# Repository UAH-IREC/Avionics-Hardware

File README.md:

# Avionics-Hardware
KiCad projects and libraries for all PCBs flying on the rocket

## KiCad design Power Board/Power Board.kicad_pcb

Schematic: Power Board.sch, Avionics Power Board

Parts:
C1: 470 µF; CP_Radial_Horiz_D8.0mm_L13.00mm_P3.50mm; Digikey Part Number 1189-1733-ND
C2, C3, C4, C5, C6, C7, C20, C21, C22, C23, C29, C30: 0.1 µF; C_0603; Digikey Part Number 1276-6717-6-ND
C8: 0.1 µF; C_0805; Digikey Part Number 478-3351-1-ND
C9, C14: 22 µF; C_0805; Digikey Part Number 1276-6780-1-ND
C10: 47 µF; C_0805; Digikey Part Number 490-13249-1-ND
C11, C12: 22nF; C_0603; Digikey Part Number 399-9044-1-ND
C13: 15 µF; C_0805; Digikey Part Number 445-14373-1-ND
C15: 1 µF; C_0603; Digikey Part Number 1276-6524-1-ND
C16, C17, C25, C26: 4.7 µF; C_0603; Digikey Part Number 1276-1900-1-ND
C18: 270 pF; C_0603; Digikey Part Number 1276-2019-1-ND
C19, C27, C28: 10 µF; C_0603; Digikey Part Number 1276-1038-1-ND
C24: 0.33 µF; C_0603; Digikey Part Number 445-12479-6-ND
D1, D4, D5, D9, D11, D12: 12V TVS; TVS_0603; Digikey Part Number 641-1256-1-ND
D2: SMBJ26A; D_SMB; Digikey Part Number SMBJ26AFSCT-ND
D3, D6, D7, D8: LED_B; LED_0603; Digikey Part Number 160-1647-1-ND
D10, D17, D18: 3.3V TVS; TVS_0402; Digikey Part Number 641-1893-1-ND
D13, D14: LED_R; LED_0603; Digikey Part Number 160-1447-1-ND
D15: D_Schottky; D_SOD-123F; Digikey Part Number CRS08QMCT-ND
D16: LED_G; LED_0603; Digikey Part Number 160-1888-1-ND
H1, H2, H3, H4: M3 Mounting Hole; MountingHole_3.2mm_M3; Digikey Part Number 732-12933-ND
HS1: Heatsink; HS_ATS1099; Digikey Part Number ATS1099-ND
J1: Conn_02x07_Odd_Even; Pin_Header_Straight_2x07_Pitch2.54mm; Digikey Part Number 952-1932-ND
J2: Screw_Terminal_01x06; 3PCV-06; Digikey Part Number 3PCV-06-006-ND
J3: Conn_01x03; JST_XH_S03B-XH-A_03x2.50mm_Angled; Digikey Part Number 455-2250-ND
J4: Conn_01x02; JST_PH_S2B-PH-K_02x2.00mm_Angled; Digikey Part Number 455-1719-ND
J5: Conn_02x03_Odd_Even; Pin_Header_Straight_2x03_Pitch1.27mm_SMD; Digikey Part Number 609-3693-1-ND
L1: 2.2 µH; L_SRP6540; Digikey Part Number SRP6540-2R2MCT-ND
L2: 15 µH; L_Wuerth_7447779115; Digikey Part Number 732-4180-1-ND
L3: 10 µH; L_SLF10165; Digikey Part Number 445-6478-1-ND
L4: 10 µH; L_1008; Digikey Part Number 490-10563-2-ND
L5: 220 Ω @ 100 MHz; L_0603; Digikey Part Number 732-1581-2-ND
Q1, Q2, Q3, Q4, Q5, Q6: SI7157DP; PowerPAK_SO-8; Digikey Part Number SI7157DP-T1-GE3CT-ND
Q7: DMG2305UX; SOT-23; Digikey Part Number DMG2305UX-13DICT-ND
R1, R2, R3, R4, R26: 1 kΩ; R_0603; Digikey Part Number RHM1.0KDCT-ND
R5, R8, R11: 82.5 kΩ; R_0603; Digikey Part Number P82.5KHCT-ND
R6, R9, R12: 5.49 kΩ; R_0603; Digikey Part Number 311-5.49KHRCT-ND
R7, R10, R13: 11 kΩ; R_0603; Digikey Part Number P11.0KHCT-ND
R14, R15, R16, R29, R30, R31: 100 kΩ; R_0603; Digikey Part Number P100KDBCT-ND
R17: 33.2 kΩ; R_0603; Digikey Part Number P33.2KHCT-ND
R18, R34, R35, R36, R38, R39, R43, R44, R45, R49, R50, R51, R53: 10 kΩ; R_0603; Digikey Part Number P10.0KHCT-ND
R19, R28: 100 Ω; R_0603; Digikey Part Number P100HCT-ND
R20: 470 Ω; R_0603; Digikey Part Number P470HCT-ND
R21: 95.3 kΩ; R_0603; Digikey Part Number P95.3KDBCT-ND
R22: 51 kΩ; R_0603; Digikey Part Number P51.0KHCT-ND
R23: 13.3 kΩ; R_0603; Digikey Part Number P13.3KDBCT-ND
R24: 0.124Ω; R_2512; Digikey Part Number A109697CT-ND
R25: 8.25 kΩ; R_0603; Digikey Part Number P8.25KDBCT-ND
R27: 22.1 kΩ; R_0603; Digikey Part Number P22.1KDBCT-ND
R32: 140 kΩ; R_0603; Digikey Part Number P140KDBCT-ND
R33: 10 Ω; R_0603; Digikey Part Number 541-10.0SCT-ND
R37: 2.5 mΩ; R_2512; Digikey Part Number A131768CT-ND
R40, R41, R42, R46, R47, R48, R52: 121 kΩ; R_0603; Digikey Part Number P121KDBCT-ND
R54, R55, R56, R57, R58, R59: 64.9 kΩ; R_0603; Digikey Part Number P64.9KDBCT-ND
SYM1: SYM_Arrow45_XLarge; Logo_v3; Digikey Part Number N/A
TH1, TH2, TH3, TH4, TH5, TH6, TH7: NXFT15XH103FA2B100; Thermistor_Through_Hole_Tiny; Digikey Part Number 490-5630-ND
U1: LTC4417CGN; SSOP-24_3.9x8.7mm_Pitch0.635mm; Digikey Part Number LTC4417CGN#PBF-ND
U2: TPS564208DDCT; SOT-23-6; Digikey Part Number 296-44123-1-ND
U3: LTC3130-1; MSOP-16-1EP_3x4mm_Pitch0.5mm; Digikey Part Number LTC3130IMSE-1#PBF-ND
U4: LMR62014XMF; SOT-23-5; Digikey Part Number LMR62014XMF/NOPBCT-ND
U5: TPS22810; SOT-23-6; Digikey Part Number 296-45304-1-ND
U6: BQ2057WSNTR; SOIC-8_3.9x4.9mm_Pitch1.27mm; Digikey Part Number 296-41202-1-ND
U7: BQ29209DRBT; Texas_S-PVSON-N8; Digikey Part Number 296-49154-1-ND
U8: LT6700CS6-1; TSOT-23-6; Digikey Part Number LT6700CS6-1#TRMPBFCT-ND
U9: STS8C5H30L; SOIC-8_3.9x4.9mm_Pitch1.27mm; Digikey Part Number 497-4398-1-ND
U10: LTC4150; MSOP-10_3x3mm_Pitch0.5mm; Digikey Part Number LTC4150CMS#PBF-ND
U11: ATxmega32E5-AU; TQFP-32_7x7mm_Pitch0.8mm; Digikey Part Number ATXMEGA32E5-AU-ND

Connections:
+3V3: C10.1, D10.1, D13.2 (A), J1.12, J1.14, J5.2, L1.2, L4.1, R14.2, R15.2, R16.2, R17.1, R36.1, R38.1, R39.1, R40.1, R54.1, R55.1, R56.1, R57.1, R58.1, R59.1
+12V: C14.1, D12.1, D14.2 (A), J1.8, R41.1, U3.14 (V_OUT)
/3V3_SENS: R40.2, R43.1, U11.6 (AREF/PA0)
/12V_SENS: R41.2, R44.1, U11.5 (PA1)
/BAL_OUT: U7.8 (OUT), U11.10 (PC6)
/BAT_BAK_VCC: C7.2, D5.1, J2.4, Q5.1 (D), R2.1, R11.2, R47.1, U1.22 (V3)
/BAT_BAK_VCC_SENS: R47.2, R50.1, U11.2 (PA4)
/BAT_CELL_1: J3.2, R31.2, R33.1, R52.1
/BAT_CELL_1_SENS: R52.2, R53.1, U11.30 (PA6)
/BAT_CELL_2: C6.2, C25.2, D4.1, Q3.1 (D), Q7.2, R3.1, R8.2, R28.2, R29.1, R30.2, R32.1, R37.2, R46.1, U1.23 (V2), U6.2 (BAT), U8.5 (Vs), U9.7 (D1), U9.8 (D1), U10.1 (SENSE+), U10.8 (VDD)
/BAT_CELL_2_CONN: J2.1, J3.3, R37.1, U10.2 (SENSE-)
/BAT_CHARGE_EN: R22.2, U4.4 (EN), U5.3, U11.20 (PR0/XTAL2)
/BAT_CHARGE_VCC: C20.1, R24.2, R25.1, U5.6, U6.3 (VCC), U6.8 (COMP)
/BAT_VCC_SENS: R46.2, R49.1, U11.3 (PA3)
/CHARGE_STAT: D16.2 (A), U6.5 (STAT), U11.9 (PC7)
/LVL_POL: R38.2, U10.6 (POL), U11.11 (PC5)
/LVL_~INT~: R36.2, U10.9 (~CLR~), U10.10 (~INT~), U11.12 (PC4)
/LVL_~SHDN~: U10.5 (~SHDN~), U11.13 (PC3)
/MCU_SCL: J1.4, U11.15 (PC1)
/MCU_SDA: J1.2, U11.16 (PC0)
/SEL_~SHDN~: U1.2 (~SHDN), U11.14 (PC2)
/SEL_~VALID1~: R16.1, U1.10 (~VALID1), U11.22 (PD6)
/SEL_~VALID2~: R15.1, U1.11 (~VALID2), U11.21 (PD7)
/SEL_~VALID3~: R14.1, U1.12 (~VALID3), U11.29 (PA7)
/THERM1: R54.2, TH2.2, U11.28 (PD0/AREF)
/THERM2: R56.2, TH4.2, U11.27 (PD1)
/THERM3: R58.2, TH6.2, U11.26 (PD2)
/THERM4: R55.2, TH3.2, U11.25 (PD3)
/THERM5: R57.2, TH5.2, U11.24 (PD4)
/THERM6: R59.2, TH7.2, U11.23 (PD5)
/UMB_VCC: C5.2, C17.1, D1.1, J2.3, L3.1, Q1.1 (D), R4.1, R5.2, R42.1, U1.24 (V1), U4.5 (VIN)
/UMB_VCC_SENS: R42.2, R45.1, U11.4 (PA2)
/VCC_IN: C1.1, C9.1, C13.1, C15.1, D2.1 (K), D9.1, D11.1, J2.6, Q2.1 (D), Q4.1 (D), Q6.1 (D), R1.1, R48.1, U1.15 (VOUT), U2.3 (VIN), U3.4 (PV_IN), U3.5 (V_IN), U3.6 (RUN), U3.8 (MPPC), U3.9 (VS2), U3.10 (VS1), U3.11 (MODE)
/VCC_IN_SENS: R48.2, R51.1, U11.31 (PA5)
GND: C1.2, C2.2, C3.2, C4.2, C5.1, C6.1, C7.1, C9.2, C10.2, C13.2, C14.2, C15.2, C16.2, C17.2, C19.2, C20.2, C22.2, C23.2, C24.2, C25.1, C27.1, C28.2, C29.1, C30.1, D1.2, D2.2 (A), D3.1 (K), D4.2, D5.2, D6.1 (K), D7.1 (K), D8.1 (K), D9.2, D10.2, D11.2, D12.2, D17.1, D18.2, J1.6, J1.10, J2.2, J2.5, J3.1, J4.2, J5.6, R7.1, R10.1, R13.1, R18.2, R19.2, R20.2, R22.1, R23.2, R26.2, R27.2, R34.1, R43.2, R44.2, R45.2, R49.2, R50.2, R51.2, R53.2, TH2.1, TH3.1, TH4.1, TH5.1, TH6.1, TH7.1, U1.3 (HYS), U1.13 (GND), U2.1 (GND), U3.1 (GND), U3.12 (EXTVCC), U3.17 (PAD), U4.2 (GND), U5.2, U6.6 (VSS), U7.5 (GND), U7.9 (PAD), U8.2 (GND), U8.3 (+INA), U9.5 (D2), U9.6 (D2), U10.7 (GND), U11.1 (GND), U11.18 (GND)
unnamed: C2.1, Q1.3 (S), Q2.3 (S), U1.21 (VS1)
unnamed: C3.1, Q3.3 (S), Q4.3 (S), U1.19 (VS2)
unnamed: C4.1, Q5.3 (S), Q6.3 (S), U1.17 (VS3)
unnamed: C8.1, U2.6 (BOOT)
unnamed: C8.2, L1.1, U2.2 (SW)
unnamed: C11.1, U3.2 (BST1)
unnamed: C11.2, L2.1, U3.3 (SW1)
unnamed: C12.1, L2.2, U3.16 (SW2)
unnamed: C12.2, U3.15 (BST2)
unnamed: C16.1, U3.7 (VCC)
unnamed: C18.1, C19.1, D15.1, R21.2, U5.1
unnamed: C18.2, R21.1, R23.1, U4.3 (FB)
unnamed: C21.1, R30.1, U7.1 (VC2)
unnamed: C21.2, C22.1, R31.1, U7.2 (VC1)
unnamed: C23.1, R28.1, U7.7 (VDD)
unnamed: C24.1, U7.4 (CD)
unnamed: C26.1, U10.3 (CF+)
unnamed: C26.2, U10.4 (CF-)
unnamed: C27.2, C29.2, D18.1, L4.2, L5.1, U11.17 (VCC)
unnamed: C28.1, C30.2, D17.2, L5.2, U11.32 (AVCC)
unnamed: D3.2 (A), R1.2
unnamed: D6.2 (A), R2.2
unnamed: D7.2 (A), R3.2
unnamed: D8.2 (A), R4.2
unnamed: D13.1 (K), R19.1
unnamed: D14.1 (K), R20.1
unnamed: D15.2, L3.2, U4.1 (SW)
unnamed: D16.1 (K), R26.1
unnamed: J4.1, R25.2, R27.1, U6.4 (TS)
unnamed: J5.1, U11.7 (PDI_DATA)
unnamed: J5.5, R39.2, U11.8 (~RESET~/PDI_CLK)
unnamed: Q1.2 (G), Q2.2 (G), U1.20 (G1)
unnamed: Q3.2 (G), Q4.2 (G), U1.18 (G2)
unnamed: Q5.2 (G), Q6.2 (G), U1.16 (G3)
unnamed: Q7.1, U6.7 (CC)
unnamed: Q7.3, R24.1, U6.1 (SNS)
unnamed: R5.1, R6.1, U1.4 (UV1)
unnamed: R6.2, R7.2, U1.5 (OV1)
unnamed: R8.1, R9.1, U1.6 (UV2)
unnamed: R9.2, R10.2, U1.7 (OV2)
unnamed: R11.1, R12.1, U1.8 (UV3)
unnamed: R12.2, R13.2, U1.9 (OV3)
unnamed: R17.2, R18.1, U2.4 (FB)
unnamed: R29.2, U7.6 (~CB_EN~), U8.6 (OUTB)
unnamed: R32.2, R34.2, U8.4 (-INB)
unnamed: R33.2, R35.2, U9.1 (S1), U9.3 (S2)
unnamed: R35.1, U7.3 (VC1_CB), U9.2 (G1), U9.4 (G2)

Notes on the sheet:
6-9 V (actually 8.4 but a little margin of error)
Needs to handle 20 A
3.3V dc-dc
12V dc-dc
Power Supply Selector: Selects the most appropriate power source between the umbilical supply, the primary battery, and the backup battery. It does this by selecting whatever source is within the preprogrammed voltage limits, in order of priority listed above. Also able to be shutdown for a time du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
Charge current 1A
Not mounted, free hanging
Cell Balance Controller
Balance MOSFETs
6V Undervoltage Cutoff
MOSFETs will need heatsinks
Close to power supply
Battery Charger: Charges the primary Lithium Polymer battery when the system is plugged into umbilical power. This is so that if the launch has to be delayed, or after a test not using umbilical power, the batteries can be recharged without opening the rocket. Features a thermistor to automatically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
Battery Balancer: Makes sure the voltage between the two cells of the battery stays almost equal. Uneven voltages can damage the battery, or even cause a fire due to overvolting the cells. The comparator at the right makes sure the cell is not attempted to be balanced below 6v, to avoid overdischar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
Battery Gas Gauge: Measures the current entering or leaving the primary battery, and outputs a pulse every time a certain number of Amp-Seconds enter or leave the battery. The MCU counts these pulses, and uses it to get a much more accurate measurement of the charge percentage of the battery than s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
Note about battery configurations: Mutually redundant: Each board's backup battery is the other's primary battery. Only two batteries in entire system. Simply redundant: Each board has two batteries, a primary and a backup. Four batteries in entire system. Simply redundant will be hotfire config. M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
Connectors: Connect to batteries and stuff
Mounting holes: M3 Screw holes. Symbol: The sweet looking rocket logo on the back.
Connector: 2x7 100mil header used to connect the different boards together
LEDs: Shows the status of the 3.3V and 12V power supplies
3.3V Power Supply: A 3.3V DC-DC Converter provides power to everything that needs 3.3V
12V Power Supply: Provides Power to analog devices on control board
Voltage Dividers: Allows the MCU to measure the voltages of all the different parts of the power supply. Sized so that the voltage is never above 1V, to be able to use the high accuracy bandgap ADC reference. Uses the same resistors for all, so that all the ADC measurements are in the same scale.
Thermistors: Allows the temperature of many parts of the power supply to be measured. Set up so that there is no maximum temperature, because as the temperature increases, the measured voltage decreases.
MCU: Measures voltages and temperatures, controls functions, and maintains a measurement of the battery capacity.
6-9 V
Battery Charger Step Up Converter: Steps up the umbilical power to a voltage high enough to charge the batteries
This resistor is in a non-standard position in order to change the behavior from on by default to off by default
High side load switch to prevent the battery charger from trying to run if the step up converter is disabled.

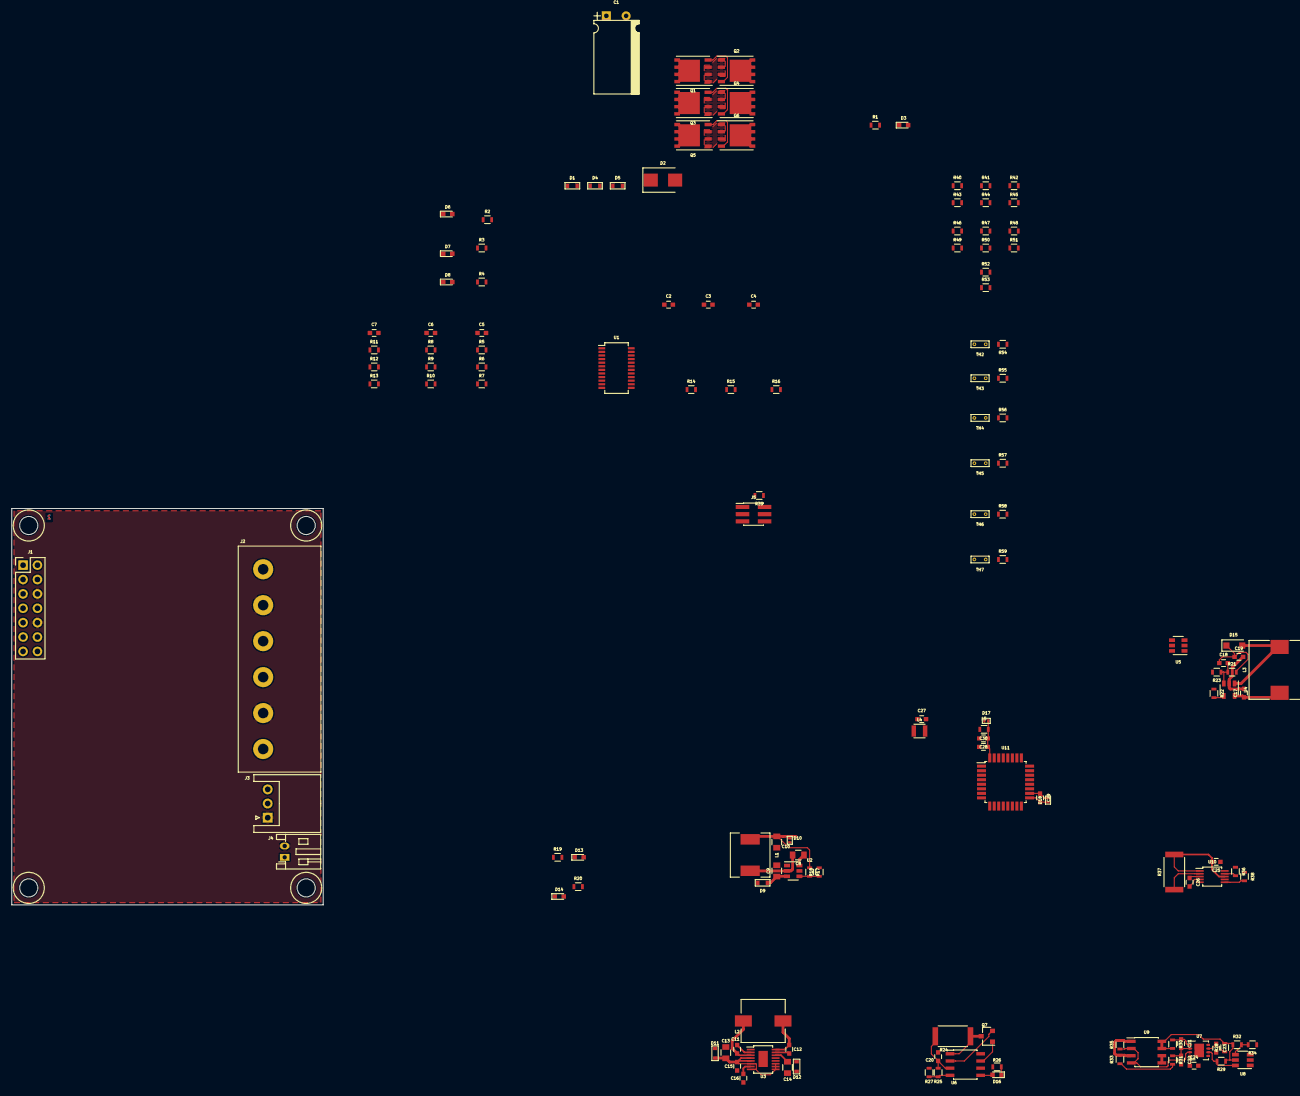
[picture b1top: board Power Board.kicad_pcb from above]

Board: 2 copper layers, 55.0 x 70.0 mm, 147 parts (1 on the bottom side), 82 nets.

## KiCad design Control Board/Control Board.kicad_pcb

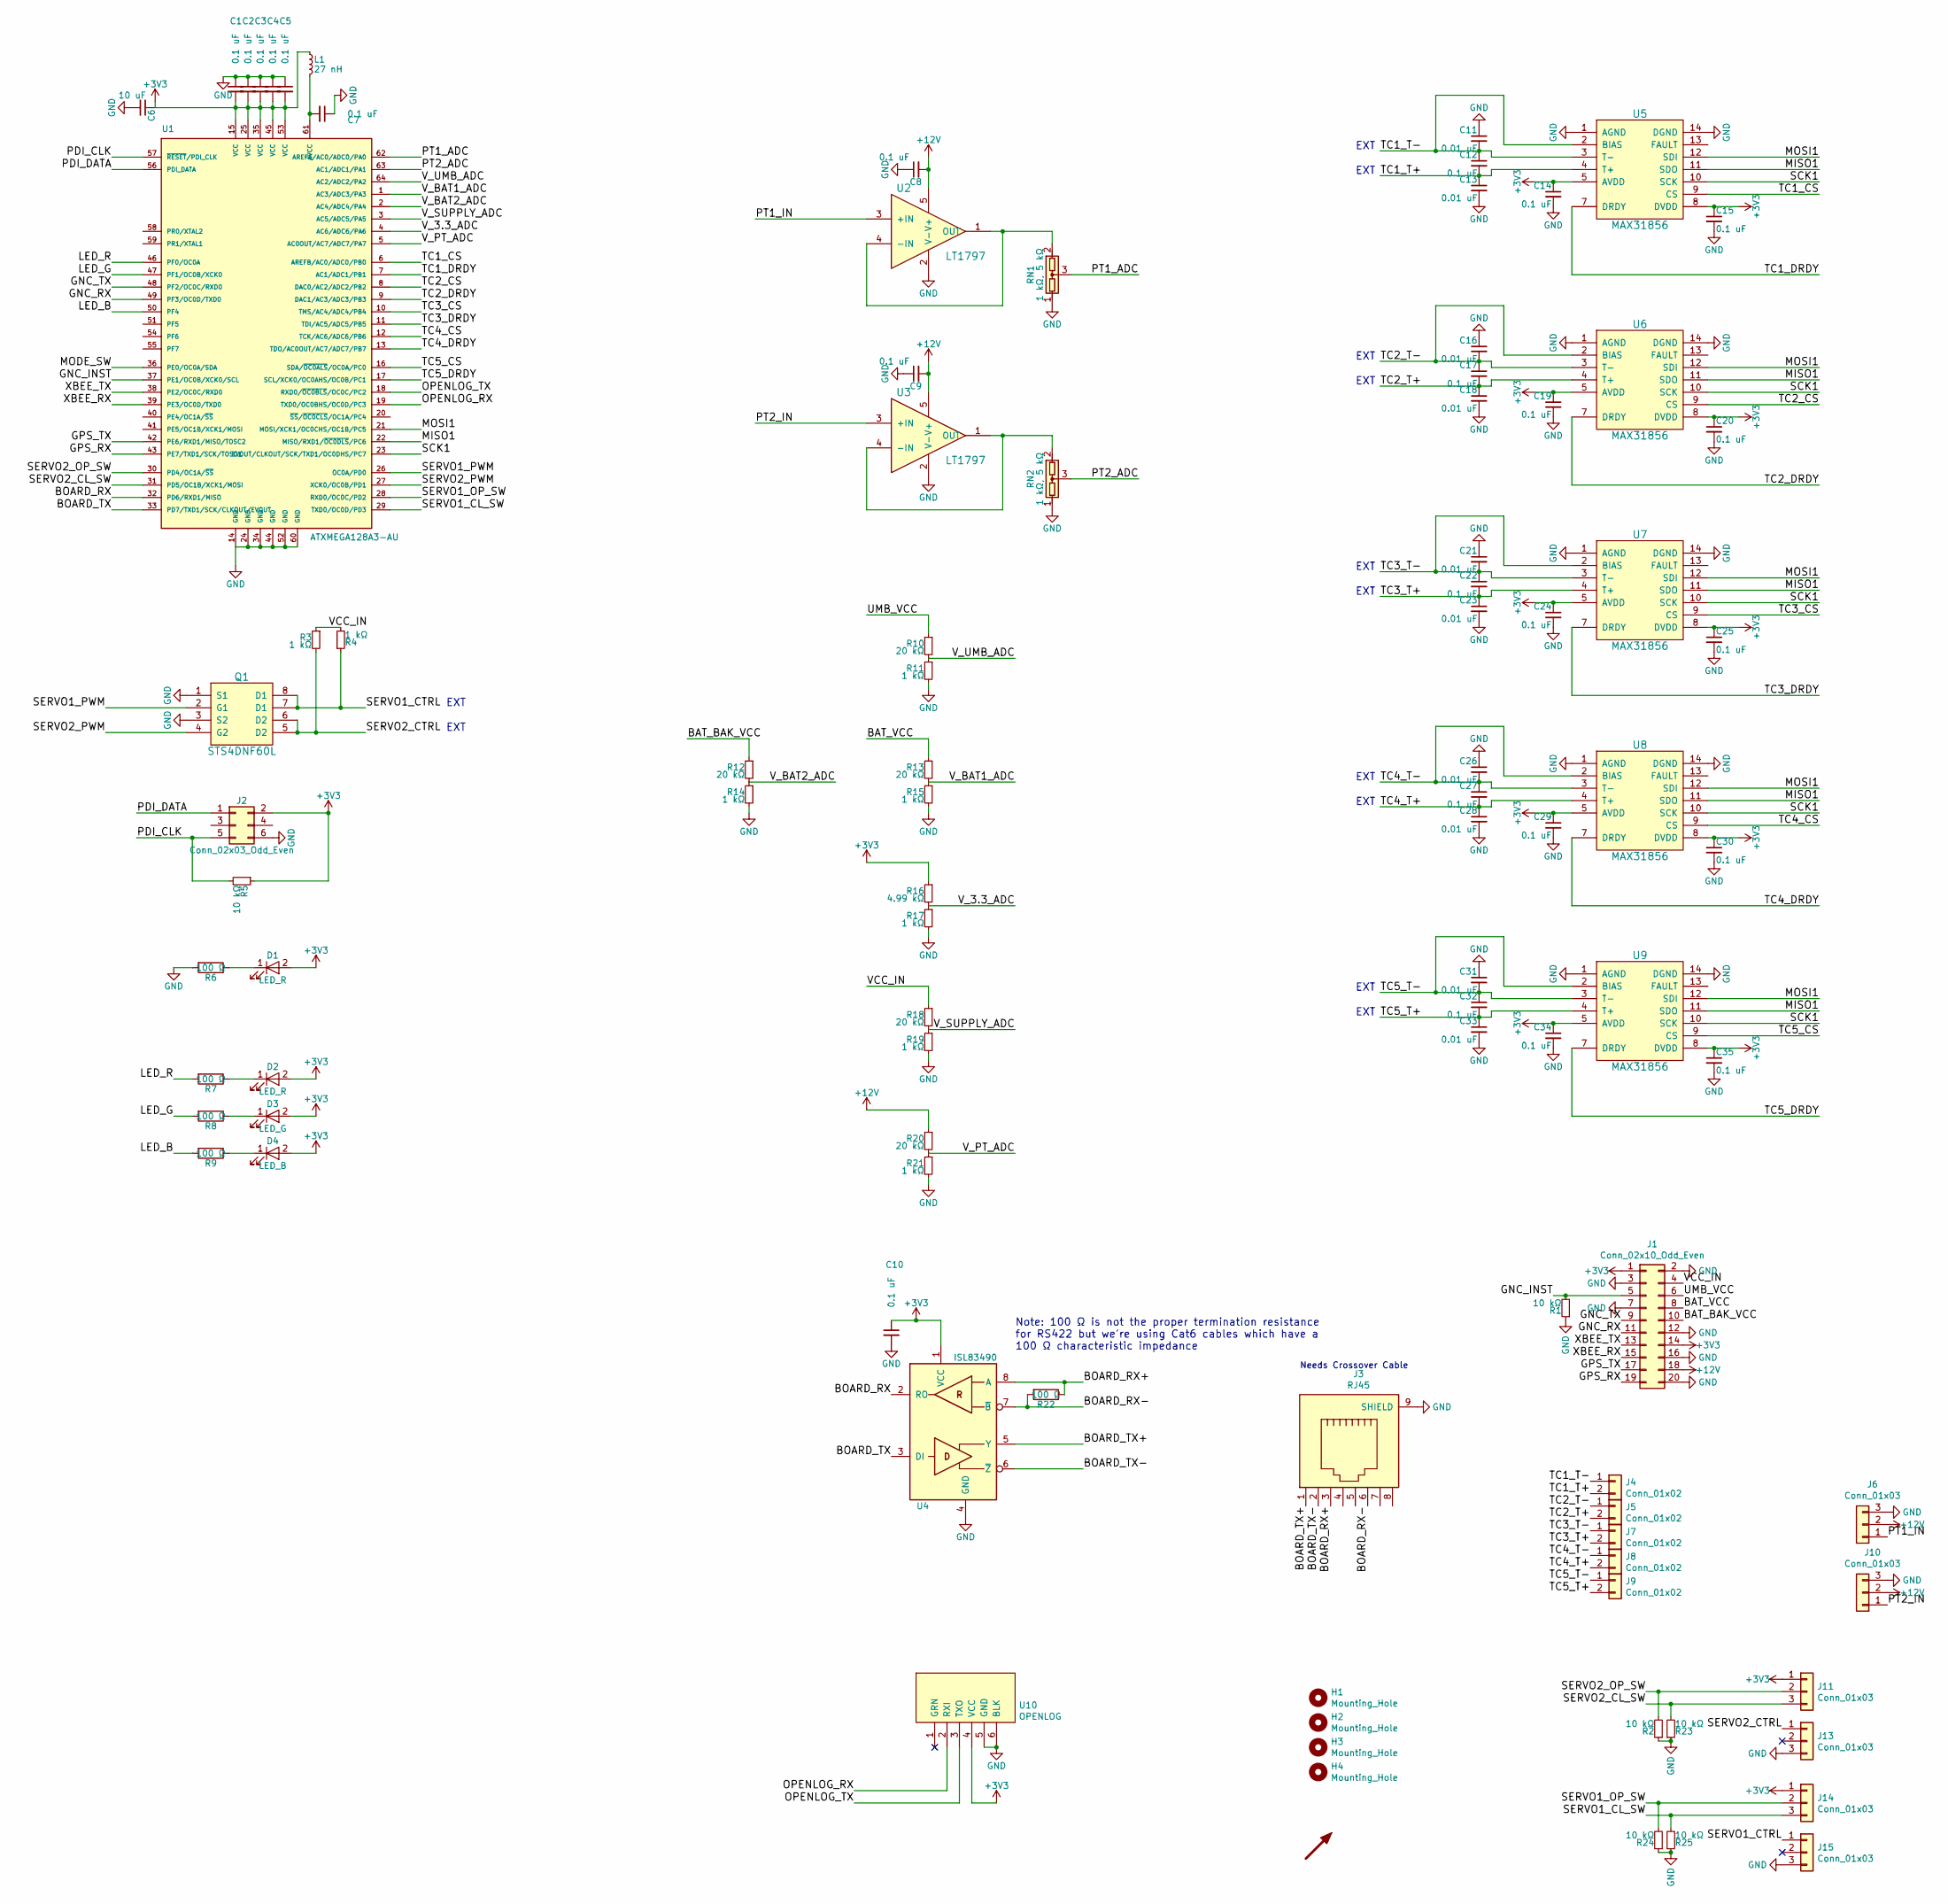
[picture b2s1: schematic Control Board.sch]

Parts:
C1, C2, C3, C4, C5, C7, C8, C9, C10, C12, C14, C15, C17, C19, C20, C22, C24, C25, C27, C29, C30, C32, C34, C35: 0.1 uF; C_0603; Digikey Part Number 445-5667-1-ND
C6: 10 uF; C_0603; Digikey Part Number 490-12323-1-ND
C11, C13, C16, C18, C21, C23, C26, C28, C31, C33: 0.01 uF; C_0603; Digikey Part Number 399-1091-1-ND
D1, D2: LED_R; LED_0603; Digikey Part Number 160-1447-1-ND
D3: LED_G; LED_0603; Digikey Part Number 160-1446-1-ND
D4: LED_B; LED_0603; Digikey Part Number 160-1647-1-ND
H1, H2, H3, H4: Mounting_Hole; MountingHole_3.2mm_M3
J1: Conn_02x10_Odd_Even; Pin_Header_Straight_2x10_Pitch1.27mm
J2: Conn_02x03_Odd_Even; Pin_Header_Angled_2x03_Pitch1.27mm; Digikey Part Number S9015E-03-ND
J3: RJ45; RJ45_8; Digikey Part Number RJHSE-5080-ND
J4, J5, J7, J8, J9: Conn_01x02; JST_PH_B2B-PH-K_02x2.00mm_Straight; Digikey Part Number 455-1719-ND
J6, J10, J11, J13, J14, J15: Conn_01x03; JST_PH_B3B-PH-K_03x2.00mm_Straight; Digikey Part Number 455-1720-ND
L1: 27 nH; L_0603; Digikey Part Number 490-1174-1-ND
Q1: STS4DNF60L; SOIC-8_3.9x4.9mm_Pitch1.27mm; Digikey Part Number 497-3226-1-ND
R1, R2, R5, R23, R24, R25: 10 kΩ; R_0603; Digikey Part Number 311-10.0KHRCT-ND
R3, R4, R11, R14, R15, R17, R19, R21: 1 kΩ; R_0603; Digikey Part Number 311-1.00KHRCT-ND
R6, R7, R8, R9: 100 Ω; R_0603; Digikey Part Number 311-100GRCT-ND
R10, R12, R13, R18, R20: 20 kΩ; R_0603; Digikey Part Number 311-20.0KHRCT-ND
R16: 4.99 kΩ; R_0603; Digikey Part Number 311-4.99KHRCT-ND
R22: 100 Ω; R_0603; Digikey Part Number 311-100HRCT-ND
RN1, RN2: 1 kΩ, 5 kΩ; SOT-23; Digikey Part Number MPMT-1K/5KCT-ND
SYM1: SYM_Arrow45_Large; Logo_v3
U1: ATXMEGA128A3-AU; TQFP-64_14x14mm_Pitch0.8mm; Digikey Part Number ATXMEGA128A3-AU-ND
U2, U3: LT1797; TSOT-23-5; Digikey Part Number LT1797CS5#TRMPBFCT-ND
U4: ISL83490; SOIC-8_3.9x4.9mm_Pitch1.27mm; Digikey Part Number ISL83490IBZ-ND
U5, U6, U7, U8, U9: MAX31856; TSSOP-14_4.4x5mm_Pitch0.65mm; Digikey Part Number MAX31856MUD+-ND
U10: OPENLOG; OpenLog; Digikey Part Number 1568-1368-ND

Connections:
+3V3: C1.2, C2.2, C3.2, C4.2, C5.2, C6.1, C10.1, C14.1, C15.1, C19.1, C20.1, C24.1, C25.1, C29.1, C30.1, C34.1, C35.1, D1.2 (A), D2.2 (A), D3.2 (A), D4.2 (A), J1.1, J1.14, J2.2, J11.1, J14.1, L1.1, R5.1, R16.1, U1.15 (VCC), U1.25 (VCC), U1.35 (VCC), U1.45 (VCC), U1.53 (VCC), U4.1 (VCC), U5.5 (AVDD), U5.8 (DVDD), U6.5 (AVDD), U6.8 (DVDD), U7.5 (AVDD), U7.8 (DVDD), U8.5 (AVDD), U8.8 (DVDD), U9.5 (AVDD), U9.8 (DVDD), U10.4 (VCC)
+12V: C8.2, C9.2, J1.18, J6.2, J10.2, R20.1, U2.5 (V+), U3.5 (V+)
/BAT_BAK_VCC: J1.10, R12.1
/BAT_VCC: J1.8, R13.1
/BOARD_RX: U1.32 (PD6/RXD1/MISO), U4.2 (RO)
/BOARD_RX+: J3.3, R22.1, U4.8 (A)
/BOARD_RX-: J3.6, R22.2, U4.7 (~B)
/BOARD_TX: U1.33 (PD7/TXD1/SCK/CLKOUT/EVOUT), U4.3 (DI)
/BOARD_TX+: J3.1, U4.5 (Y)
/BOARD_TX-: J3.2, U4.6 (~Z~)
/GNC_INST: J1.5, R1.2, U1.37 (PE1/OC0B/XCK0/SCL)
/GNC_RX: J1.11, U1.49 (PF3/OC0D/TXD0)
/GNC_TX: J1.9, U1.48 (PF2/OC0C/RXD0)
/GPS_RX: J1.19, U1.43 (PE7/TXD1/SCK/TOSC1)
/GPS_TX: J1.17, U1.42 (PE6/RXD1/MISO/TOSC2)
/LED_B: R9.2, U1.50 (PF4)
/LED_G: R8.2, U1.47 (PF1/OC0B/XCK0)
/LED_R: R7.2, U1.46 (PF0/OC0A)
/MISO1: U1.22 (MISO/RXD1/~OC0DLS~/PC6), U5.11 (SDO), U6.11 (SDO), U7.11 (SDO), U8.11 (SDO), U9.11 (SDO)
/MODE_SW: U1.36 (PE0/OC0A/SDA)
/MOSI1: U1.21 (MOSI/XCK1/OC0CHS/OC1B/PC5), U5.12 (SDI), U6.12 (SDI), U7.12 (SDI), U8.12 (SDI), U9.12 (SDI)
/OPENLOG_RX: U1.19 (TXD0/OC0BHS/OC0D/PC3), U10.2 (RXI)
/OPENLOG_TX: U1.18 (RXD0/~OC0BLS~/OC0C/PC2), U10.3 (TXO)
/PDI_CLK: J2.5, R5.2, U1.57 (~RESET~/PDI_CLK)
/PDI_DATA: J2.1, U1.56 (PDI_DATA)
/PT1_ADC: RN1.3, U1.62 (AREFA/AC0/ADC0/PA0)
/PT1_IN: J6.1, U2.3 (+IN)
/PT2_ADC: RN2.3, U1.63 (AC1/ADC1/PA1)
/PT2_IN: J10.1, U3.3 (+IN)
/SCK1: U1.23 (EVOUT/CLKOUT/SCK/TXD1/OC0DHS/PC7), U5.10 (SCK), U6.10 (SCK), U7.10 (SCK), U8.10 (SCK), U9.10 (SCK)
/SERVO1_CL_SW: J14.3, R25.2, U1.29 (TXD0/OC0D/PD3)
/SERVO1_CTRL: J15.1, Q1.7 (D1), Q1.8 (D1), R4.1
/SERVO1_OP_SW: J14.2, R24.2, U1.28 (RXD0/OC0C/PD2)
/SERVO1_PWM: Q1.2 (G1), U1.26 (OC0A/PD0)
/SERVO2_CL_SW: J11.3, R23.2, U1.31 (PD5/OC1B/XCK1/MOSI)
/SERVO2_CTRL: J13.1, Q1.5 (D2), Q1.6 (D2), R3.2
/SERVO2_OP_SW: J11.2, R2.2, U1.30 (PD4/OC1A/~SS~)
/SERVO2_PWM: Q1.4 (G2), U1.27 (XCK0/OC0B/PD1)
/TC1_CS: U1.6 (AREFB/AC0/ADC0/PB0), U5.9 (CS)
/TC1_DRDY: U1.7 (AC1/ADC1/PB1), U5.7 (DRDY)
/TC1_T+: C12.2, C13.1, J4.2, U5.4 (T+)
/TC1_T-: C11.2, C12.1, J4.1, U5.2 (BIAS), U5.3 (T-)
/TC2_CS: U1.8 (DAC0/AC2/ADC2/PB2), U6.9 (CS)
/TC2_DRDY: U1.9 (DAC1/AC3/ADC3/PB3), U6.7 (DRDY)
/TC2_T+: C17.2, C18.1, J5.2, U6.4 (T+)
/TC2_T-: C16.2, C17.1, J5.1, U6.2 (BIAS), U6.3 (T-)
/TC3_CS: U1.10 (TMS/AC4/ADC4/PB4), U7.9 (CS)
/TC3_DRDY: U1.11 (TDI/AC5/ADC5/PB5), U7.7 (DRDY)
/TC3_T+: C22.2, C23.1, J7.2, U7.4 (T+)
/TC3_T-: C21.2, C22.1, J7.1, U7.2 (BIAS), U7.3 (T-)
/TC4_CS: U1.12 (TCK/AC6/ADC6/PB6), U8.9 (CS)
/TC4_DRDY: U1.13 (TDO/AC0OUT/AC7/ADC7/PB7), U8.7 (DRDY)
/TC4_T+: C27.2, C28.1, J8.2, U8.4 (T+)
/TC4_T-: C26.2, C27.1, J8.1, U8.2 (BIAS), U8.3 (T-)
/TC5_CS: U1.16 (SDA/~OC0ALS~/OC0A/PC0), U9.9 (CS)
/TC5_DRDY: U1.17 (SCL/XCK0/OC0AHS/OC0B/PC1), U9.7 (DRDY)
/TC5_T+: C32.2, C33.1, J9.2, U9.4 (T+)
/TC5_T-: C31.2, C32.1, J9.1, U9.2 (BIAS), U9.3 (T-)
/UMB_VCC: J1.6, R10.1
/VCC_IN: J1.4, R3.1, R4.2, R18.1
/V_3.3_ADC: R16.2, R17.1, U1.4 (AC6/ADC6/PA6)
/V_BAT1_ADC: R13.2, R15.1, U1.1 (AC3/ADC3/PA3)
/V_BAT2_ADC: R12.2, R14.1, U1.2 (AC4/ADC4/PA4)
/V_PT_ADC: R20.2, R21.1, U1.5 (AC0OUT/AC7/ADC7/PA7)
/V_SUPPLY_ADC: R18.2, R19.1, U1.3 (AC5/ADC5/PA5)
/V_UMB_ADC: R10.2, R11.1, U1.64 (AC2/ADC2/PA2)
/XBEE_RX: J1.15, U1.39 (PE3/OC0D/TXD0)
/XBEE_TX: J1.13, U1.38 (PE2/OC0C/RXD0)
GND: C1.1, C2.1, C3.1, C4.1, C5.1, C6.2, C7.1, C8.1, C9.1, C10.2, C11.1, C13.2, C14.2, C15.2, C16.1, C18.2, C19.2, C20.2, C21.1, C23.2, C24.2, C25.2, C26.1, C28.2, C29.2, C30.2, C31.1, C33.2, C34.2, C35.2, J1.2, J1.3, J1.7, J1.12, J1.16, J1.20, J2.6, J3.9 (SHIELD), J6.3, J10.3, J13.3, J15.3, Q1.1 (S1), Q1.3 (S2), R1.1, R2.1, R6.2, R11.2, R14.2, R15.2, R17.2, R19.2, R21.2, R23.1, R24.1, R25.1, RN1.1, RN2.1, U1.14 (GND), U1.24 (GND), U1.34 (GND), U1.44 (GND), U1.52 (GND), U1.60 (GND), U2.2 (V-), U3.2 (V-), U4.4 (GND), U5.1 (AGND), U5.14 (DGND), U6.1 (AGND), U6.14 (DGND), U7.1 (AGND), U7.14 (DGND), U8.1 (AGND), U8.14 (DGND), U9.1 (AGND), U9.14 (DGND), U10.5 (GND), U10.6 (BLK)
unnamed: C7.2, L1.2, U1.61 (AVCC)
unnamed: D1.1 (K), R6.1
unnamed: D2.1 (K), R7.1
unnamed: D3.1 (K), R8.1
unnamed: D4.1 (K), R9.1
unnamed: RN1.2, U2.1 (OUT), U2.4 (-IN)
unnamed: RN2.2, U3.1 (OUT), U3.4 (-IN)

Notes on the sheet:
EXT
Note: 100 Ω is not the proper termination resistance for RS422 but we're using Cat6 cables which have a 100 Ω characteristic impedance
Needs Crossover Cable

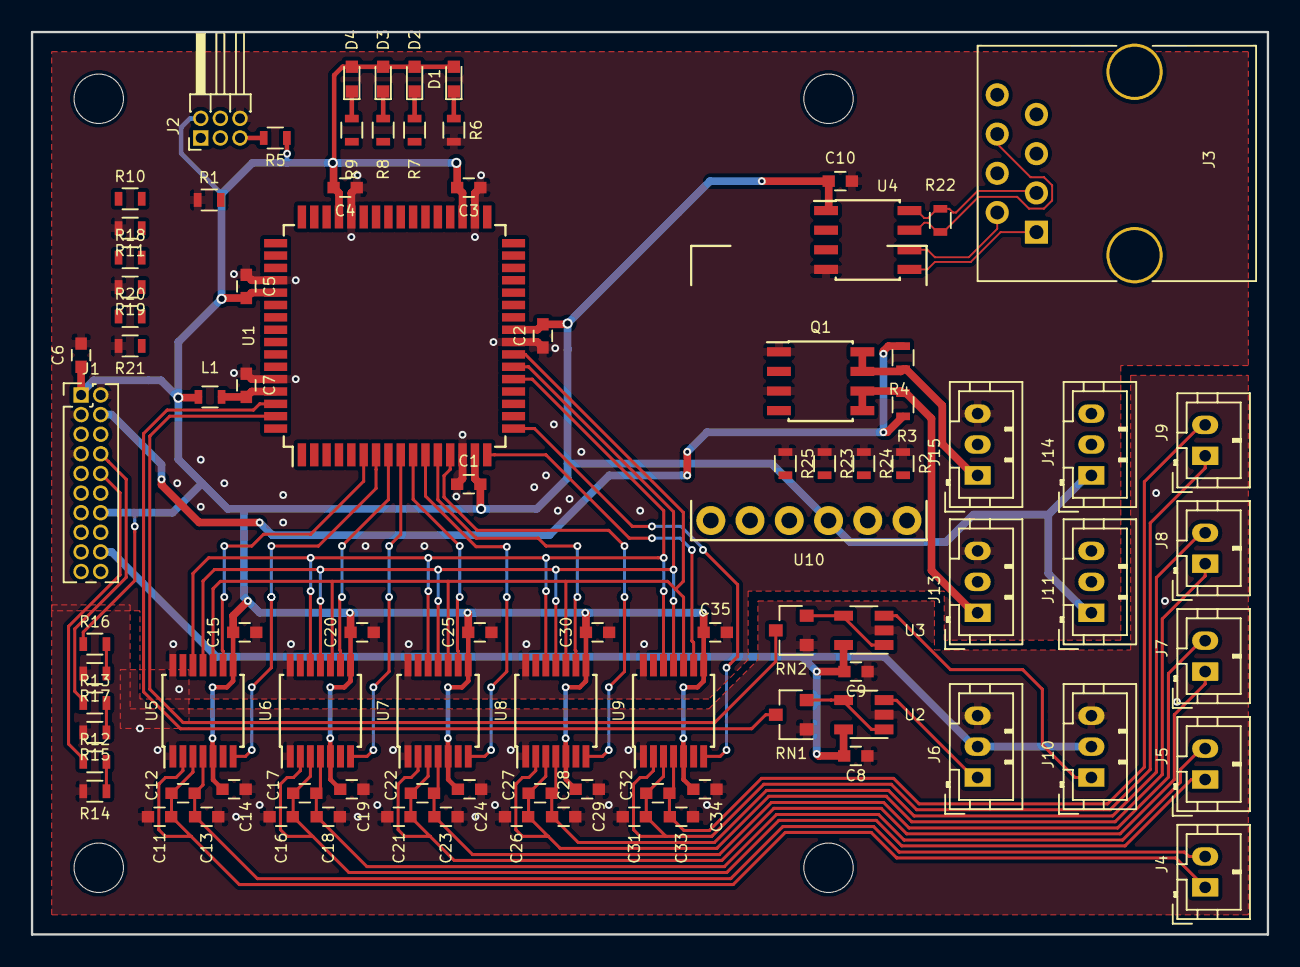
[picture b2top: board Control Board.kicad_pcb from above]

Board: 2 copper layers, 80.0 x 58.4 mm, 97 parts (1 on the bottom side), 75 nets.
